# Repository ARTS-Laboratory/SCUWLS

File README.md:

# SWaP-Constrained UAV-deployable Water-Level Sensor (SCUWLS)
UAV Deployable Stage Height Sensor with Magnetic Docking Mechanism

This work is discussed in two papers:
1. Md Asifuzzaman Khan, Muhammad Usman Khan, Amanda Sarka, P. G. Tien Tran, Michelle Eigbe, Austin R. J. Downey, Jason D. Bakos, Erick Blasche, and Jasim Imran. Energy budget analysis of swap-constrained UAV-deployable water-level sensors with varying sampling intervals and idle currents. In SPIE Defense + Commercial Sensing 2026. SPIE, 2026
2. Corinne Smith, Joud Satme, Jacob Martin, Austin R.J. Downey, Nikolaos Vitzilaios, and Jasim Imran. UAV rapidly-deployable stage sensor with electro-permanent magnet docking mechanism for flood monitoring in undersampled watersheds. HardwareX, 12:e00325, oct 2022. doi:10.1016/j.ohx.2022.e00325.

## Hardware

<p align="center">
Figure 1: The "Georgetown Version 0.5" of the sensor, showing  (a) the assembled sensor package and (b) a cross-section view of the sensor.
</p>

<p align="center">
Figure 2: Sensors deployed for continuous monitoring in the Charleston, SC area.
</p>

<p align="center">
Figure 3: Drone delivering a sensor package underneath a structure using an Electro Permanent Magnet docking mechanism.
</p>

## Versions 

### V0
1. Data logging saved onto SD card
2. Battery monitoring
3. Solar load sharing
4. Measures stage, temperature, pressure, humidity
5. EPM with wireless toggling to attach under structures

### V1 (projected)
1. Adaptive sampling algorithm
2. Wireless data transfer with GUI
3. Camera integration

## Licensing and Citation

[![CC BY-SA 4.0][cc-by-sa-shield]][cc-by-sa]

This work is licensed under a
[Creative Commons Attribution-ShareAlike 4.0 International License][cc-by-sa].

[cc-by-sa]: http://creativecommons.org/licenses/by-sa/4.0/
[cc-by-sa-image]: https://licensebuttons.net/l/by-sa/4.0/88x31.png
[cc-by-sa-shield]: https://img.shields.io/badge/License-CC%20BY--SA%204.0-lightgrey.svg

Cite as:

@Misc{ARTSLabSwapConstrainedUav,     
  author = {{ARTS-L}ab},  
  howpublished = {GitHub},  
  title  = {{SWaP-Constrained UAV-deployable Water-Level Sensor (SCUWLS)}},    
  groups = {{ARTS-L}ab},    
  url    = {https://github.com/ARTS-Laboratory/SWaP-Constrained-UAV-deployable-Water-Level-Sensor},   
}

<br>

<p align="center">
https://github.com/ARTS-Laboratory/UAV-Deployable-Stage-Height-Sensor
</p>

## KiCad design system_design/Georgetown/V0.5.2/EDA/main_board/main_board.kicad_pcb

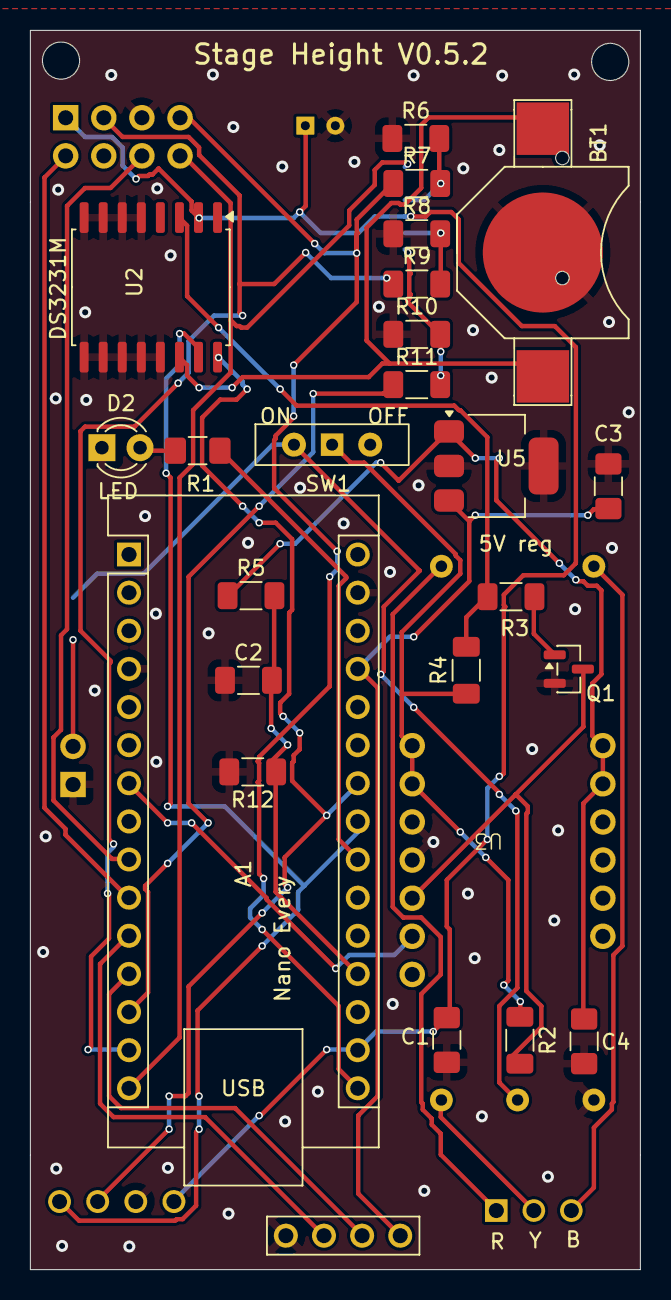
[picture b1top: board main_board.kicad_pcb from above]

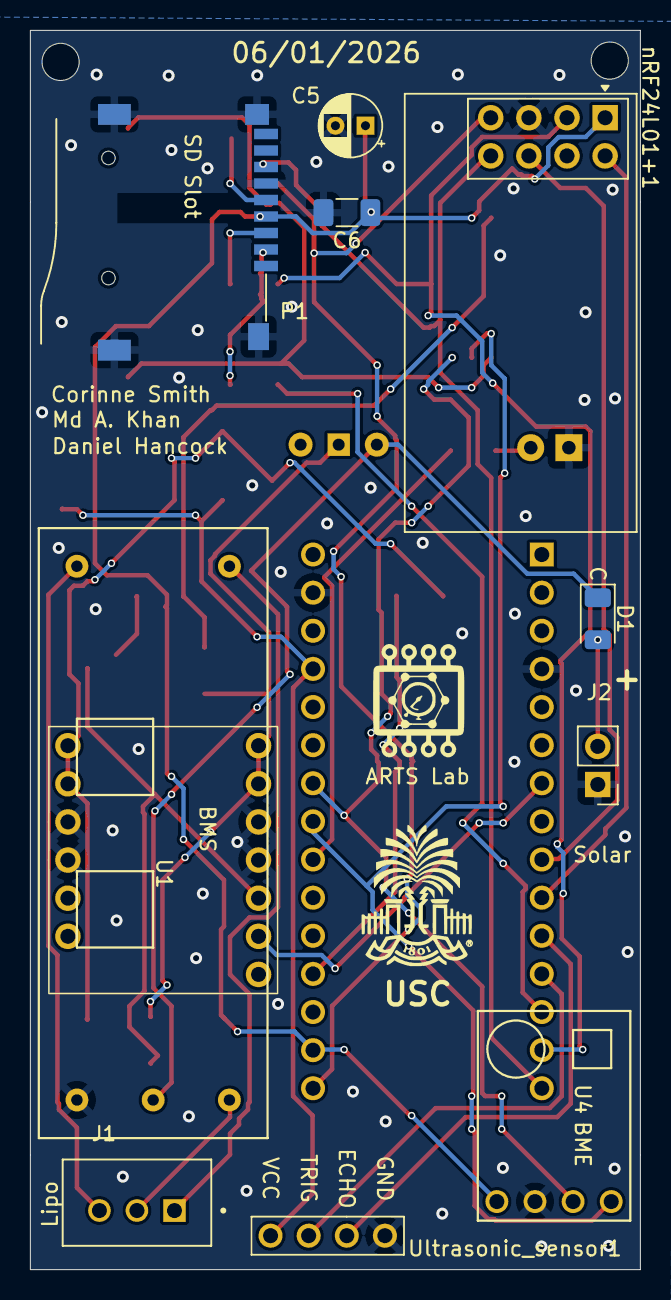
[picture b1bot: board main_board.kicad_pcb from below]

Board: 2 copper layers, 40.6 x 82.6 mm, 36 parts (13 on the bottom side), 31 nets.

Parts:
A1: Arduino_Nano_v2.x-MCU_Module; Arduino_Nano
ARTS Lab: LOGO
BT1: Battery_Cell; battery_holder_10mm
C1, C4: 0.1uF; C_1206_3216Metric_Pad1.42x1.75mm_HandSolder
C2, C6: 0.1uF; C_1206_3216Metric_Pad1.33x1.80mm_HandSolder
C3: 22uF; C_1206_3216Metric_Pad1.42x1.75mm_HandSolder
C5: 10uF; CP_Radial_D4.0mm_P2.00mm
D1: D_Schottky; D_1206_3216Metric
D2: LED; LED_D3.0mm
J1: B3B-XH-A_LF__SN_; XH2.54
J2: Conn_01x02_Pin; PinHeader_1x02_P2.54mm_Vertical
P1: SD card socket; SUNTECH_ST-TF-003A
Q1: MMBT2222A; SOT-23
R1: 1k; C_1206_3216Metric_Pad1.42x1.75mm_HandSolder
R2, R4: 100k; C_1206_3216Metric_Pad1.33x1.80mm_HandSolder
R3, R5, R12: 10k; C_1206_3216Metric_Pad1.33x1.80mm_HandSolder
R6, R8, R10: 2K; C_1206_3216Metric_Pad1.33x1.80mm_HandSolder
R7, R9, R11: 1K; C_1206_3216Metric_Pad1.33x1.80mm_HandSolder
SW1: SW_Wuerth_450301014042; SW_Slide-03_Wuerth-WS-SLTV_10x2.5x6.4_P2.54mm
U1: HX-2S-JH10
U2: DS3231M; SOIC-16W_7.5x10.3mm_P1.27mm
U3: Polou LV switch psw03a
U4: BME280_module
U5: KA78M05_TO252; SOT-223-3_TabPin2
USC: UofSC; LOGO
Ultrasonic_sensor1: HCSR04
nRF24L01+1: nRF24L01+; nRF24L01_Breakout

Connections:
3V3: A1.17 (3V3), C1.1, C5.1, C6.1, P1.4 (VDD), U2.2 (VCC), U4.1 (VIN), nRF24L01+1.1 (3.3V)
5V: A1.27 (+5V), C3.2, U5.3 (VO), Ultrasonic_sensor1.4 (VCC)
Alarm_INT: R3.2, R4.2, U2.3 (~INT/SQW)
GND: A1.4 (GND), A1.29 (GND), BT1.2 (-), C1.2, C2.1, C3.1, C4.1, C5.2, C6.2, D2.1 (K), J2.1, P1.6 (VSS), P1.G1 (GND), P1.G2 (GND), P1.G3 (GND), P1.G4 (GND), Q1.2 (E), R6.1, R8.1, R10.1, R12.2, U1.1 (P-), U2.5 (GND), U2.6 (GND), U2.7 (GND), U2.8 (GND), U2.9 (GND), U2.10 (GND), U2.11 (GND), U2.12 (GND), U2.13 (GND), U3.3 (GND), U3.4 (GND), U3.9 (GND), U3.10 (GND), U4.2 (GND), U5.2 (GND), Ultrasonic_sensor1.1 (GND), nRF24L01+1.5 (GND)
MISO: A1.15 (D12), P1.7 (DAT0/MISO), nRF24L01+1.8 (MISO)
MOSI: A1.14 (D11), R9.1, nRF24L01+1.3 (MOSI)
unnamed: A1.19 (A0), C2.2, R5.2, R12.1
unnamed: A1.22 (A3), R1.1
unnamed: A1.23 (A4), U2.15 (SDA), U4.4 (SDA)
unnamed: A1.24 (A5), U2.16 (SCL), U4.3 (SCL)
unnamed: A1.7 (D4), U3.12 (Off)
unnamed: A1.11 (D8), Ultrasonic_sensor1.2 (ECHO)
unnamed: A1.12 (D9), Ultrasonic_sensor1.3 (TRIG)
unnamed: BT1.1 (+), U2.14 (VBAT)
unnamed: D1.2 (A), J2.2
unnamed: D1.1 (K), SW1.2 (C), U1.2 (P+)
unnamed: D2.2 (A), R1.2
unnamed: P1.5 (CLK/SCK), R6.2, R7.2
unnamed: P1.3 (CMD/MOSI), R8.2, R9.2
unnamed: P1.2 (DAT3/CS), R10.2, R11.2
unnamed: Q1.1 (B), R3.1
unnamed: Q1.3 (C), R2.2, U3.11 (On)
unnamed: R2.1, R4.1, SW1.1 (B), U3.7 (Vin), U3.8 (Vin)
unnamed: J1.1, U1.5 (B+)
unnamed: J1.3, U1.3 (B-)
unnamed: J1.2, U1.4 (BM)
unnamed: C4.2, R5.1, U3.1 (Vout), U3.2 (Vout), U5.1 (VI)
SCK: A1.16 (D13), R7.1, nRF24L01+1.7 (SCK)
SD_CS: A1.13 (D10), R11.1
nRF_CE: A1.9 (D6), nRF24L01+1.6 (CE)
nRF_CS: A1.10 (D7), nRF24L01+1.2 (CSN)

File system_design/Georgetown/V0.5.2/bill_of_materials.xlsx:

Part Designator | Component | manufacturer part number | Amount | Unit | Individual Cost | Total Cost | Vendor 1 | Vendor 2 | Vendor 3 | Vendor 4 | Vendor 5 | Vendor 6
Nano every | Arduino Nano every |  | 1 | Pc | 12.9 | 12.9 | https://store-usa.arduino.cc/products/nano-every?srsltid=AU7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 | https://www.sparkfun.com/arduino-nano-every.html?utm_source=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
P1 (Micro SD card slot) | 112J-TDAR-R01, 9 (8 + 1) Position Card Connector Secure Digital - microSD™ Surf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 |  | 1 | Pc | 2.52 | 2.52 | https://www.digikey.com/en/products/detail/attend-technology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 | https://www.ebay.com/itm/235081679206?chn=ps&var=53609137009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
NRF24L01+ | NRF24L01+ 2.4GHz Wireless RF Transceiver Module |  | 1 | Pc | 1.4 | 1.4 | https://www.amazon.com/Makerfire-Arduino-NRF24L01-Wireless-T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 | https://www.digikey.com/en/products/detail/ai-thinker/NF-01-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 | https://www.ebay.com/itm/185777140664?_trkparms=amclksrc%3DI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
U2 (DS3231) | DS3231M+ real-time clock IC |  | 1 | Pc | 11.96 | 11.96 | https://www.digikey.com/en/products/detail/analog-devices-in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 | https://www.mouser.com/ProductDetail/Analog-Devices-Maxim-In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
U4 (BME280) | BME280 Pressure, Temperature and Humidity sensor |  | 1 | Pc | 5.26 | 5.26 | https://www.ebay.com/itm/327147846952?_skw=BME280+5+V&itmmet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 | https://www.amazon.com/Onyehn-Temperature-Humidity-Barometri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 | https://www.ebay.com/itm/223602242983?chn=ps&norover=1&mkevt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 | https://www.ebay.com/itm/183678893844?chn=ps&mkevt=1&mkcid=2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 | https://protosupplies.com/product/bme280-i2c-pressure-humidi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
U3 | Mini Pushbutton Power Switch with Reverse Voltage Protection, LV |  | 1 | Pc | 4.95 | 4.95 | https://www.digikey.com/en/products/detail/pololu/2808/10450608 | https://www.pololu.com/product/2808
N42 permanent magnet | Neodymium Disc Magnet - 1 1/4" Dia x 3/8" Thi |  | 1 | Pc | 15.2 | 15.2 | https://www.kjmagnetics.com/dx46-neodymium-disc-magnet?srslt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
Ultrasonic sensor | HC-SR04 |  | 1 | Pc | 5.25 | 5.25 | Ultrasonic Distance Sensor - 5V (HC-SR04) | https://www.digikey.com/en/products/detail/adafruit-industri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 | https://www.ebay.com/itm/192312930293?chn=ps&mkevt=1&mkcid=2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
2s 7.4V LiPo battery | 2S Lipo Battery 1500mAh 7.4V with Deans Plug, Dim: 69*35*18mm |  | 1 | Pc | 18 | 18 | https://zeeebattery.com/products/zeee-7-4v-60c-1500mah-2s-li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 | https://www.ebay.com/itm/383205406858
CR-1025 3V Li+ coin cell | CR-1025-ND |  | 1 | Pc | 1.0900000000000001 | 1.0900000000000001 | CR1025 Jauch Quartz | Battery Products | DigiKey | https://www.ebay.com/itm/365610739537?chn=ps&mkevt=1&mkcid=2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
BT1 (coin cell holder) | BK-870 |  | 1 | Pc | 0.57999999999999996 | 0.57999999999999996 | BK-870 MPD (Memory Protection Devices) | Battery Products | DigiKey | https://www.ebay.com/itm/133891769676?chn=ps&mkevt=1&mkcid=2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
Q1 | MMBT2222A NPN transistor |  | 1 | pc | 0.14000000000000001 | 0.14000000000000001 | https://www.digikey.com/en/products/detail/diotec-semiconduc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
PCB stage height v0.5.2 | Main board |  | 1 | Pc | 8.23 | 8.23 | https://oshpark.com/
Micro SD card | 8GB Micro SD Card |  | 1 | Pc | 8.24 | 8.24 | https://www.staples.com/centon-micro-8gb-sdhc-memory-card-uh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 | https://www.staples.com/transcend-8gb-microsdhc-memory-card-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 | https://www.cdwg.com/product/transcend-flash-memory-card-8-g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 | https://www.cdwg.com/product/kingston-industrial-flash-memor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 | https://business.walmart.com/ip/Gigastone-8GB-Micro-SD-Card-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 | https://www.amazon.com/Gigastone-10-Pack-Surveillance-Securi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
SW1 (Slide switch) | 450301014042, Slide Switch SPDT Through Hole |  | 1 | Pc | 2.0299999999999998 | 2.0299999999999998 | https://www.digikey.com/en/products/detail/w%C3%BCrth-elektr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 | https://www.mouser.com/ProductDetail/Wurth-Elektronik/450301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
D2 (LED) | L314ED, 3mm Red LED |  | 1 | Pc | 0.2 | 0.2 | L314ED American Opto Plus LED | Optoelectronics | DigiKey Marketplace | https://www.lvelectronics.com/details/item?itemid=AOP%20L314ED
R3, R5, R12 | RES SMD (10k) OHM 1% 1/4W 1206 |  | 3 | Pc | 0.1 | 0.30000000000000004 | https://www.digikey.com/en/products/detail/yageo/RC1206FR-07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
R6, R8, R10 | RES SMD (2K) OHM 1% 1/4W 1206 |  | 3 | Pc | 0.1 | 0.30000000000000004 | https://www.digikey.com/en/products/detail/bourns-inc/CR1206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 | https://www.mouser.com/ProductDetail/KOA-Speer/RK73H2BLTD200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
R1, R7, R9, R11 | RES SMD (1k) OHM 1% 1/4W 1206 |  | 4 | Pc | 0.1 | 0.4 | https://www.digikey.com/en/products/detail/bourns-inc/CR1206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 | https://www.mouser.com/ProductDetail/YAGEO/SR1206FR-071KL?qs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
R2, R4 | RES SMD (100k) OHM 1% 1/4W 1206 |  | 2 | Pc | 0.1 | 0.2 | https://www.digikey.com/en/products/detail/yageo/RC1206FR-07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
D1 (schottky) | Diode 20 V 1A Surface Mount 1206 (3216 Metric) |  | 1 | Pc | 0.39 | 0.39 | https://www.digikey.com/en/products/detail/kyocera-avx/SD120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 | https://www.mouser.com/ProductDetail/KYOCERA-AVX/SD1206T020S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
C3 (polarized) | 22 µF Molded Tantalum Capacitors 6.3 V 1206 (3216 Metric) 3Ohm |  | 1 | Pc | 0.41 | 0.41 | https://www.digikey.com/en/products/detail/kyocera-avx/TAJA2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 | https://www.mouser.com/ProductDetail/KYOCERA-AVX/TAJA226K006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
C5 | 10 µF 25 V Aluminum Electrolytic Capacitors Radial, Can 1000 Hrs @ 85°C |  | 1 | Pc | 0.26 | 0.26 | https://www.digikey.com/en/products/detail/panasonic-electro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 | https://www.mouser.com/ProductDetail/Panasonic/ECE-A1EKS100B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
C1, C2, C4, C6 | C1206S104K5RACAUTO 0.1 uF 10% 50V Ceramic Capacitor X7R 1206 (3216 Metric) |  | 4 | Pc | 0.48 | 1.92 | C1206S104K5RACAUTO KEMET | Capacitors | DigiKey | https://www.mouser.com/ProductDetail/KEMET/C1206S104K5RACAUT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
U5 | Linear Voltage Regulator IC Positive Fixed 1 Output 500mA SOT-223-3 |  | 1 | Pc | 3.58 | 3.58 | MIC5239-5.0YS-TR Microchip Technology | Integrated Circuits (ICs) | DigiKey | https://www.microchipdirect.com/product/MIC5239-5.0YS-TR?srs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 | https://www.mouser.com/ProductDetail/Microchip-Technology/MI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
PVC pipe | Schedule 40 Clear Pipe, Non-threaded |  | 1 | Pc | 60.76 | 60.76 | https://www.grainger.com/product/1AAZ8?gucid=N:N:PS:Paid:GGL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
Female HC-SR04 connector | SSA-104-W-T, 4 pin connector |  | 1 | Pc | 0.91 | 0.91 | SSA-104-W-T Samtec Inc. | Connectors, Interconnects | DigiKey | https://www.samtec.com/products/ssa-104-w-t
U1 (BMS) | HX-2S-JH10 |  | 1 | Pc | 2.15 | 2.15 | https://www.ebay.com/itm/122175451692?_skw=2s+7.4v+bms&itmme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 | https://www.ebay.com/itm/386425796959?_trkparms=amclksrc%3DI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
J2 (solar) | B2B-XH-A, 2.54mm JST 2 pin |  | 1 | Pc | 0.1 | 0.1 | https://www.digikey.com/en/products/detail/jst-sales-america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
J1 (Lipo) | B3B-XH-A, 2.54mm JST 3 pin |  | 1 | Pc | 0.13 | 0.13 | https://www.digikey.com/en/products/detail/jst-sales-america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 | https://www.ebay.com/itm/135516167050?_skw=B3B-XH-A&itmmeta=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
Solar panels | SM141K06TF |  | 9 | Pc | 7.39 | 66.509999999999991 | https://www.digikey.com/en/products/detail/anysolar-ltd/SM14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
 | M3 Hex nut |  | 2 | Pc | 0.01 | 0.02
 | M3 screw |  | 2 | Pc | 0.01 | 0.02
 | M2 hex nut |  | 2 | Pc | 0.01 | 0.02 | https://www.grainger.com/product/Hex-Nut-M2-0-40-Thread-6CA66
 | M2 screw |  | 4 | Pc | 7.2999999999999995E-2 | 0.29199999999999998 | https://www.grainger.com/product/Machine-Screws-M2x0-40-Thre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
O-Rings | O-Ring: Buna-N, Round, 2 mm C.S., 35 mm I.D. |  | 1 | Pc | 2.68 | 2.68 | https://www.grainger.com/product/O-Ring-Buna-N-41KW27
Chipolo tracker | Chipolo POP |  | 1 | Pc | 25 | 25 | https://chipolo.net/en-us/products/chipolo-pop?variant=4000996
 |  |  |  |  | Total Cost | 264.30200000000002
